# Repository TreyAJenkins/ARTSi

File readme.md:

# ARTSi  Automated Radar Terminal Service interface
---

Provides an interface between an ARTS Keyboard & Trackball to a modern PC using USB HID emulation.

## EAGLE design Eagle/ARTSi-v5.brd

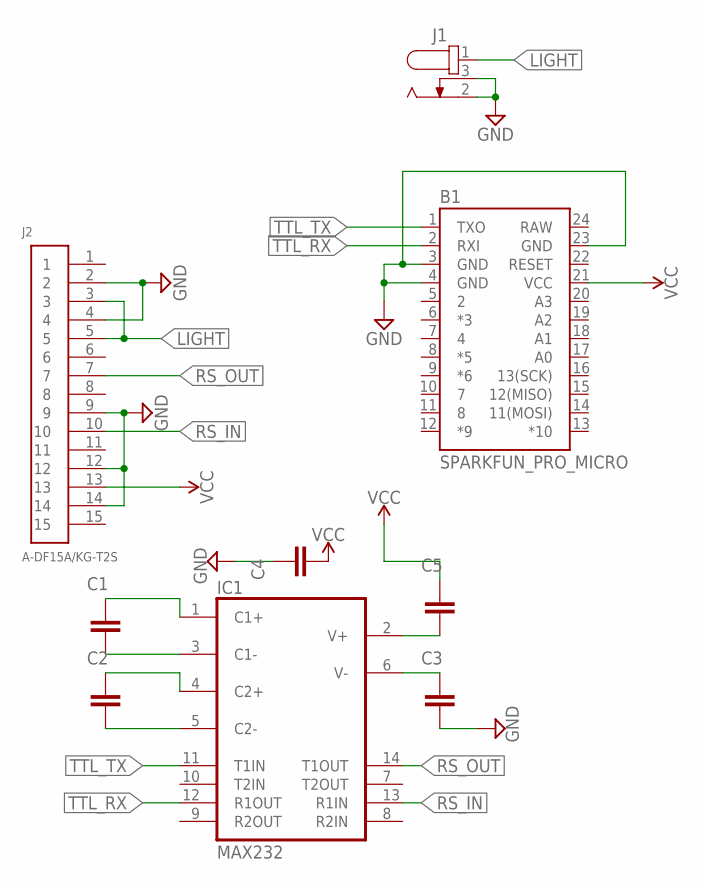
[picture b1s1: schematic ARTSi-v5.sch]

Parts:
B1: SPARKFUN_PRO_MICRO
C1, C2, C3, C4, C5: CC0805KRX7R9BB104; CAP_0805
IC1: MAX232; DIL16
J1: 694108301002
J2: A-DF15A/KG-T2S

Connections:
GND: B1.3 (GND), B1.4 (GND), B1.23 (GND), C3.2, C4.1, IC1.15 (GND), J1.2, J1.3, J2.2, J2.4, J2.9, J2.12, J2.14
LIGHT: J1.1, J2.3, J2.5
unnamed: C1.2, IC1.3 (C1-)
unnamed: C2.1, IC1.4 (C2+)
unnamed: C2.2, IC1.5 (C2-)
unnamed: C1.1, IC1.1 (C1+)
unnamed: C5.2, IC1.2 (V+)
unnamed: C3.1, IC1.6 (V-)
RAW: B1.24 (RAW)
RS_IN: IC1.13 (R1IN), J2.10
RS_OUT: IC1.14 (T1OUT), J2.7
TTL_RX: B1.2 (RXI), IC1.12 (R1OUT)
TTL_TX: B1.1 (TXO), IC1.11 (T1IN)
VCC: B1.21 (VCC), C4.2, C5.1, IC1.16 (VCC), J2.13

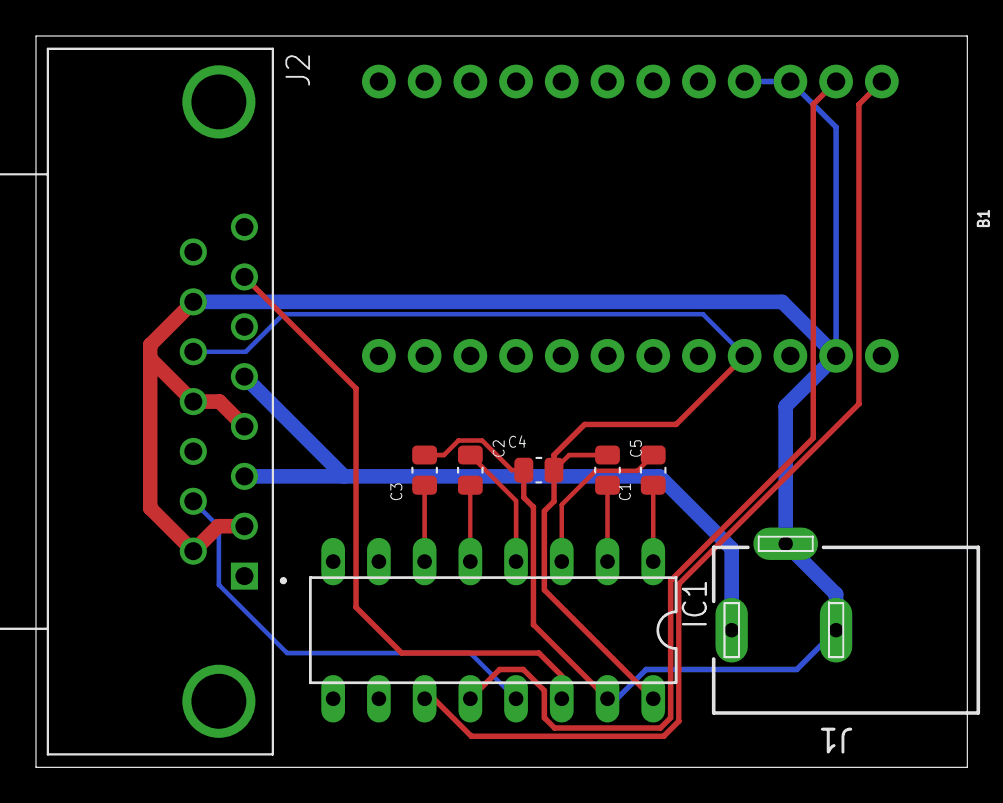
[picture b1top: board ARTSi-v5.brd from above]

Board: 2 copper layers, 51.7 x 40.6 mm, 9 parts (0 on the bottom side), 13 nets.

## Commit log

2021-01-09 disabled eeprom
2021-01-09 Remapped asterisk key
2021-01-09 Remapped VFR and IFR key
2021-01-22 Added ERAM
2021-01-23 Added mode select
2021-01-23 Fixed mode select
2021-01-23 Fixed character input
2021-01-23 removed passthrough function

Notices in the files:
parts and their libraries:
Wurth_Connectors_WR-DC: Copyright: Würth Elektronik
SparkFun-Boards: Licensing: Creative Commons ShareAlike 4.0 International - https://creativecommons.org/licenses/by-sa/4.0
